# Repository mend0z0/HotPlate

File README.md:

## Latest update

``
Mainly working on Firmware, but modifying file structures and updating readme files are also on-going...
``

# HotPlate

Hot plate project's purpose is to control the temperature of a hot plate that is used for reflow soldering of PCBs in small numbers. The application
will support a camera for more analysis and study of the process of soldering. The application accepts Gerber, Pick&Place, and BOM, so then the 
user will have a full assembly guideline and also with the connected camera it's possible to confirm the quality and validity of placement and assembly.

## Category

__Assembly Automation__

## Features

- Image processing
- Manual assembly guide
- Controlling over any kind of heaters

## Tech Stack

### Hardware

- **MCU:** PIC18F24J50
- **Connection:** USB, SPI
- **PCB Layers:** 4Layer/s (None-controlled Impedance)
- **CAD:** KiCAD

### Firmware

- **OS:** Super loop
- **Programming Language:** C Language
- **IDE:** MPLABX

### Application

- **IDE:** Qt6
- **Operating System:** Linux/Windows
- **Device:** PC/Laptop

### Mechanical

- **CAD:** Solid Edge
- **Manufacturing Method:** 3D Printing

## Block Diagrams

## Screenshots

### Hardware

#### Hardware CAD View

#### 3D_View

#### Assembled Hardware

### Mechanical CAD View

### Final Device

### Application

## Demo

## LOGO

## Author

- [@Siavash Taher Parvar](https://www.linkedin.com/in/mend0z0)

## Support

[Support Link](https://github.com/sponsors/mend0z0)

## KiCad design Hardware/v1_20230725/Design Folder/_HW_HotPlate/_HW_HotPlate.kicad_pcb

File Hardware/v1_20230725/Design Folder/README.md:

# TODO list

HotPlate hardware project todo list.

## Tasks

- #### MUST DO (List the works that proper working of project depends on these tasks):
    - Removing the Header 4x2 from Mechanical parts, and replacing with only 1 recept 1x8.
    - Adding all the mechanical components to the library and schematic.
    - Exporting all the required outputs and finalizing the hardware project.
    - Designing the enclosure in Solidedge.
    - Correcting the stencil outputs. (Next revision)
    - 
- #### Important (List the works that efficient and optimized functionality of project depends on these tasks):
    - Adding 1 more RED LED for +5v power to be placed on the enclosure. (Mechanical parts) (Next revision)
    - Adding 1 more header (2x1, P1.27mm), for +5v output in schematic. (Next revision)
    - Adding Test points for each output power. (Next revision)
    - Correcting the prog pin order according to the output of the programmer. (Next revision)
    - Sizing up the components to 0603 package. (Next revision)
    - Changing the LDO to some bigger package, maybe TL... (Next revision)
    - Modifying the component placement for sure :) (Next revision)
    - Changing the big cap (10uF_400V) to THD. (Next revision)
    - 
- #### General (List tasks that are good to be done but the functionality of project doesn't depend on these):
    - 
    -
    -

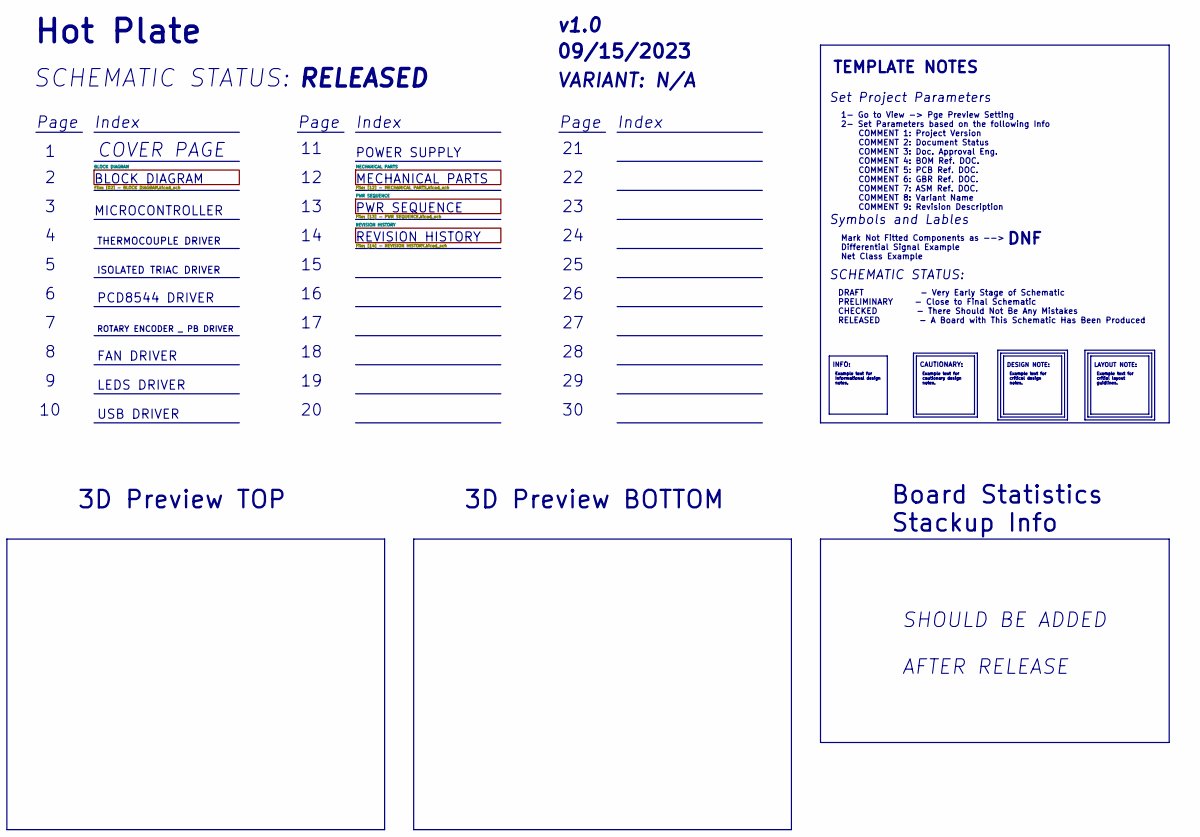
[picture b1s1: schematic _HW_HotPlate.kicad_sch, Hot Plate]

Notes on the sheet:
USB DRIVER
SHOULD BE ADDED AFTER RELEASE
Set Project Parameters
PCD8544 DRIVER
PWR SEQUENCE
VARIANT: ${COMMENT8}
${REVISION}
Index
Example text for critial layout guidlines.
${TITLE}
DESIGN NOTE:
Page
Board Statistics Stackup Info
REVISION HISTORY
${COMMENT2}
COVER PAGE
SCHEMATIC STATUS:
ISOLATED TRIAC DRIVER
MICROCONTROLLER
LEDS DRIVER
Symbols and Lables
TEMPLATE NOTES
THERMOCOUPLE DRIVER
Mark Not Fitted Components as --> Differential Signal Example Net Class Example
${ISSUE_DATE}
Example text for critical design notes.
Example text for Informational design notes.
Example text for cautionary design notes.
INFO:
SCHEMATIC STATUS:
BLOCK DIAGRAM
FAN DRIVER
3D Preview BOTTOM
1- Go to View -> Pge Preview Setting 2- Set Parameters based on the following Info COMMENT 1: Project Version COMMENT 2: Document Status COMMENT 3: Doc. Approval Eng. COMMENT 4: BOM Ref. DOC. COMMENT 5: PCB Ref. DOC. COMMENT 6: GBR Ref. DOC. COMMENT 7: ASM Ref. DOC. COMMENT 8: Variant Name COMMENT 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
LAYOUT NOTE:
CAUTIONARY:
POWER SUPPLY
DRAFT - Very Early Stage of Schematic PRELIMINARY - Close to Final Schematic CHECKED - There Should Not Be Any Mistakes RELEASED - A Board with This Schematic Has Been Produced
MECHANICAL PARTS
DNF

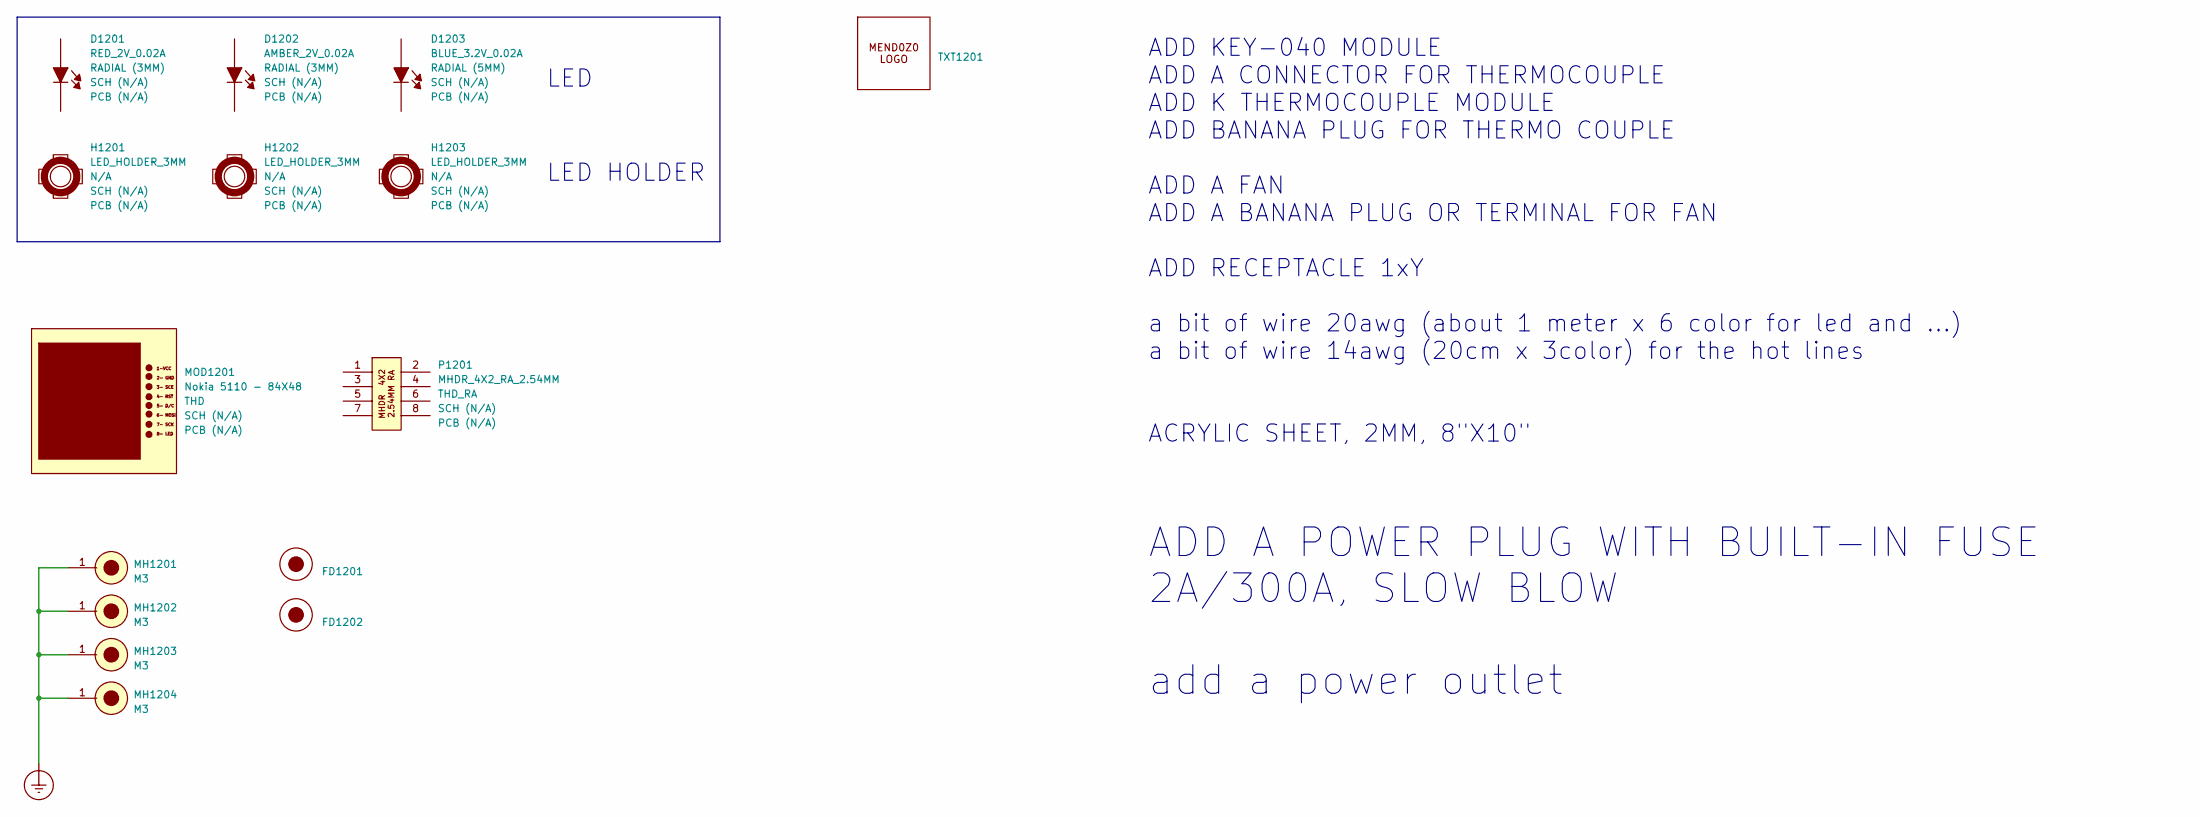
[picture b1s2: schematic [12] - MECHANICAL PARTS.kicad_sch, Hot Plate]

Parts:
D1201: RED_2V_0.02A; LED_D3.0mm; Part Number (Manufactur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 WP7113ID
D1202: AMBER_2V_0.02A; LED_D3.0mm; Part Number (Manufactur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 BL-BJC1V4V-AT
D1203: BLUE_3.2V_0.02A; LED_D5.0mm; Part Number (Manufactur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 151051BS04000
FD1201, FD1202: Fiducial_0.5mm_Mask1mm
H1201, H1202, H1203: LED_HOLDER_3MM; Part Number (Manufactur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 SSH-LX3050
MH1201, MH1202, MH1203, MH1204: M3; MountingHole_3.2mm_M3_DIN965_Pad_TopBottom
MOD1201: Nokia 5110 - 84X48; Part Number Graphic LCD 84x48 - Nokia 5110
P1201: MHDR_4X2_RA_2.54MM; PinHeader_2x04_P2.54mm_Horizontal; Part Number (Manufactur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 PHED-RS008G1ABOGA-C006
TXT1201: Mend0z0_Logo

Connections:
Earth_Protective: MH1201.1, MH1202.1, MH1203.1, MH1204.1; also elsewhere on the board

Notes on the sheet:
LED
ADD KEY-040 MODULE ADD A CONNECTOR FOR THERMOCOUPLE ADD K THERMOCOUPLE MODULE ADD BANANA PLUG FOR THERMO COUPLE ADD A FAN ADD A BANANA PLUG OR TERMINAL FOR FAN ADD RECEPTACLE 1xY a bit of wire 20awg (about 1 meter x 6 color for led and ...) a bit of wire 14awg (20cm x 3color) for the hot lines ACRY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
LED HOLDER
ADD A POWER PLUG WITH BUILT-IN FUSE 2A/300A, SLOW BLOW add a power outlet

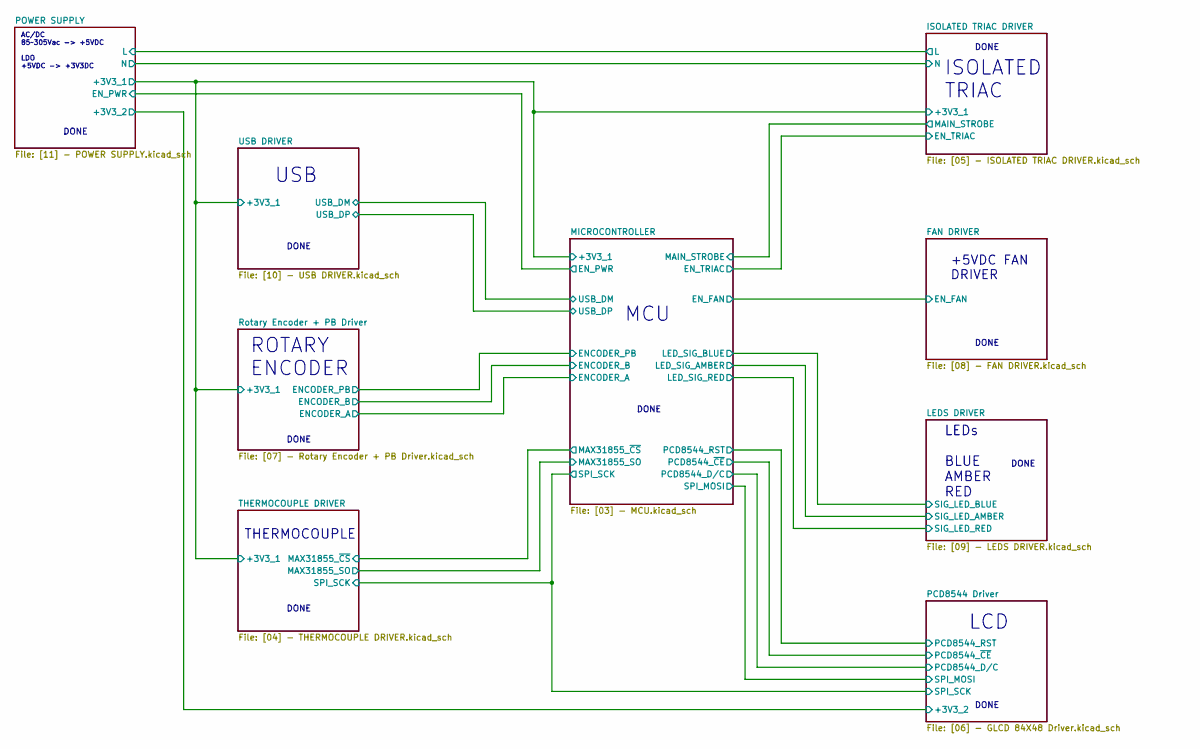
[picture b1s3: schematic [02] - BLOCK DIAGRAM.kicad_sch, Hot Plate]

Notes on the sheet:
DONE
MCU
THERMOCOUPLE
AC/DC 85~305Vac -> +5VDC LDO +5VDC -> +3V3DC
USB
LCD
ROTARY ENCODER
ISOLATED TRIAC
LEDs BLUE AMBER RED
+5VDC FAN DRIVER

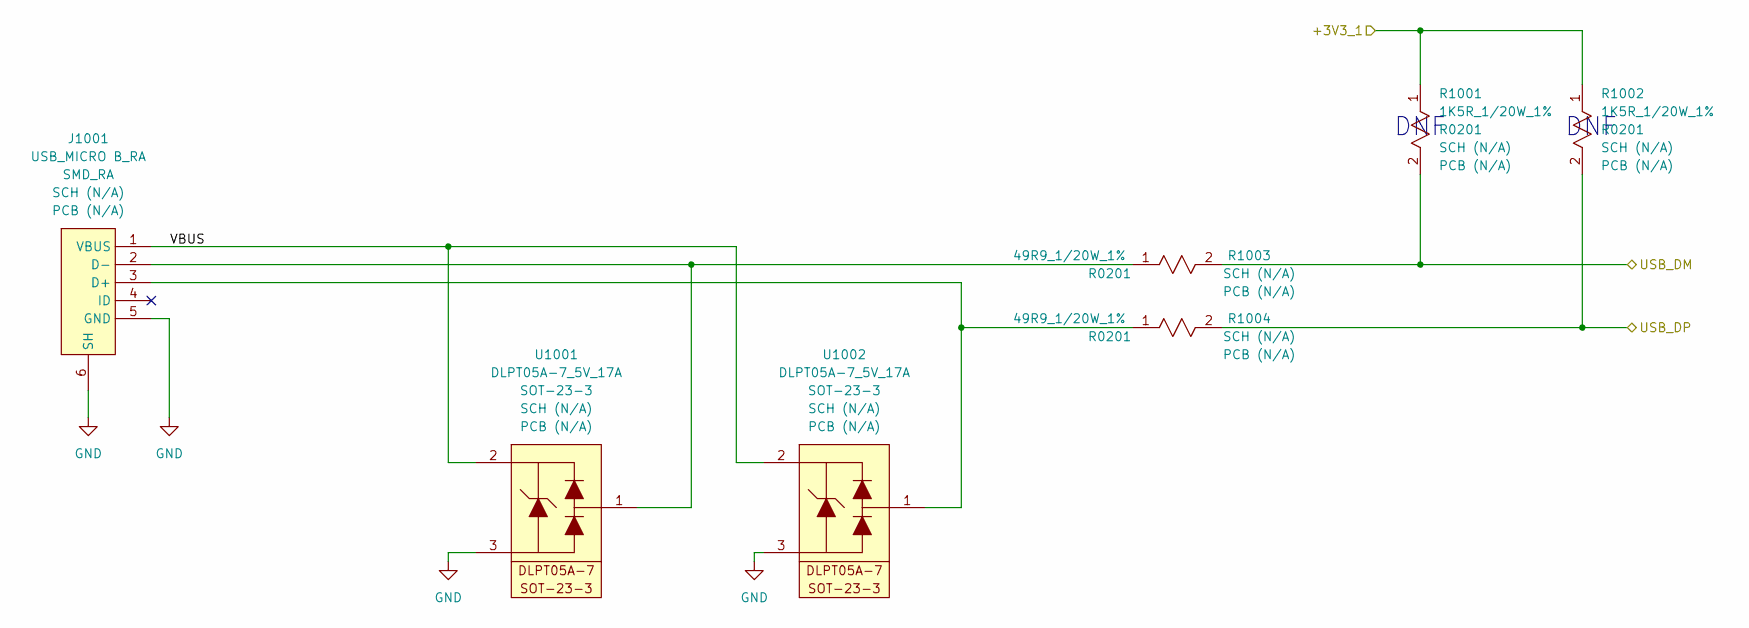
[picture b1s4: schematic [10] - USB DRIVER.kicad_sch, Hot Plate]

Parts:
J1001: USB_MICRO B_RA; USB_Micro-B_Amphenol_10118194_Horizontal; Part Number (Manufactur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 10118194-0001LF
R1001, R1002: 1K5R_1/20W_1%; R_0201_0603Metric; Part Number (Manufactur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 RC0201FR-071K4L
R1003, R1004: 49R9_1/20W_1%; R_0201_0603Metric; Part Number (Manufactur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 RMCF0201FT49R9
U1001, U1002: DLPT05A-7_5V_17A; SOT-23; Part Number (Manufactur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 DLPT05A-7

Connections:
/BLOCK DIAGRAM/ISOLATED TRIAC DRIVER/+3V3_1: R1001.1, R1002.1; also elsewhere on the board
/BLOCK DIAGRAM/MICROCONTROLLER/USB_DM: R1001.2, R1003.2; also elsewhere on the board
/BLOCK DIAGRAM/MICROCONTROLLER/USB_DP: R1002.2, R1004.2; also elsewhere on the board
/BLOCK DIAGRAM/USB DRIVER/VBUS: J1001.1 (VBUS), U1001.2, U1002.2
unnamed: J1001.3 (D+), R1004.1, U1002.1
unnamed: J1001.2 (D-), R1003.1, U1001.1

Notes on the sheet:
DNF

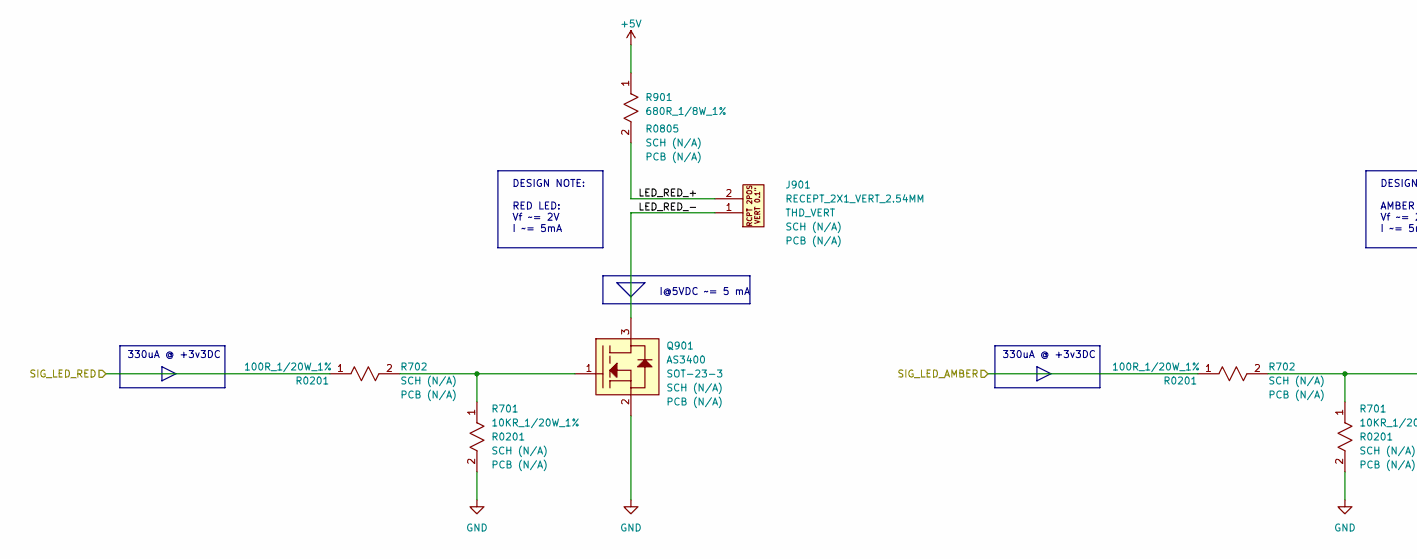
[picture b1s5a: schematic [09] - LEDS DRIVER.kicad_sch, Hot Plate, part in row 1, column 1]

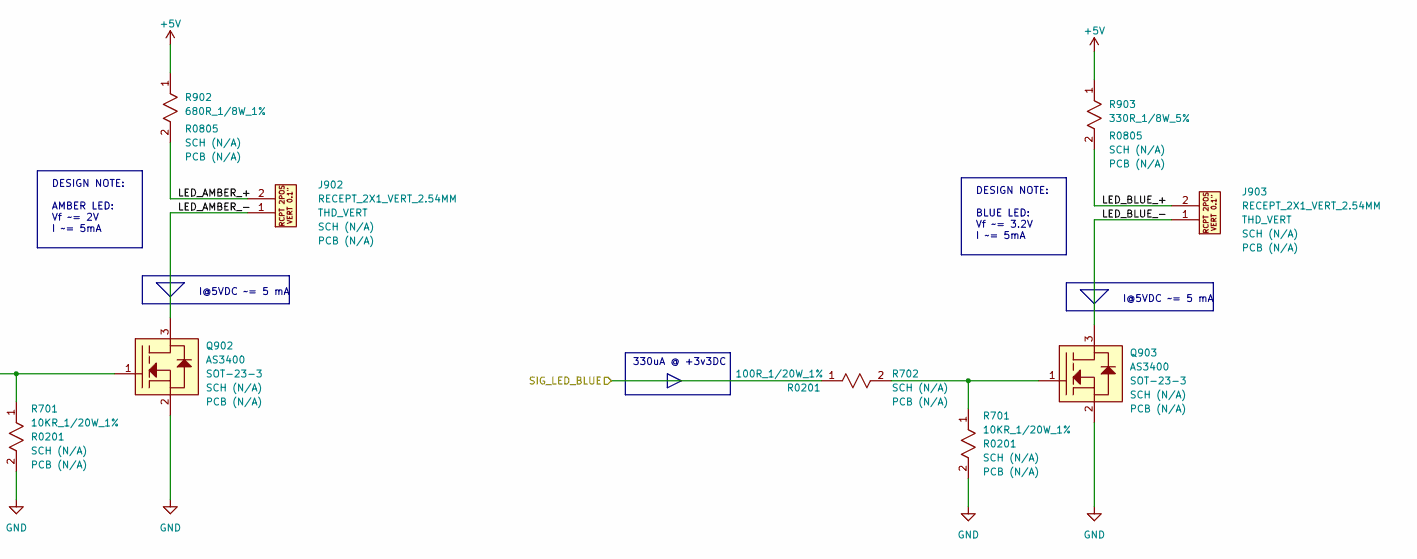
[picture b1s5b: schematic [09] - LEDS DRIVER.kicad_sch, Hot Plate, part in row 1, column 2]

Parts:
J901, J902, J903: RECEPT_2X1_VERT_2.54MM; PinSocket_1x02_P2.54mm_Vertical; Part Number (Manufactur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 RS1-02-G
Q901, Q902, Q903: AS3400; SOT-23; Part Number (Manufactur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 AS3400
R701: 10KR_1/20W_1%; R_0201_0603Metric; Part Number (Manufactur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 RMCF0201FT10K0
R702: 100R_1/20W_1%; R_0201_0603Metric; Part Number (Manufactur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 RMCF0201FT100R
R901, R902: 680R_1/8W_1%; R_0805_2012Metric; Part Number (Manufactur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 AC0805FR-07680RL
R903: 330R_1/8W_5%; R_0805_2012Metric; Part Number (Manufactur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 CRGCQ0805J330R

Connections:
/BLOCK DIAGRAM/LEDS DRIVER/LED_AMBER_+: J902.2, R902.2
/BLOCK DIAGRAM/LEDS DRIVER/LED_AMBER_-: J902.1, Q902.3
/BLOCK DIAGRAM/LEDS DRIVER/LED_RED_+: J901.2, R901.2
/BLOCK DIAGRAM/LEDS DRIVER/LED_RED_-: J901.1, Q901.3
unnamed 68: R702.1; also elsewhere on the board

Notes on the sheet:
DESIGN NOTE: AMBER LED: Vf ~= 2V I ~= 5mA
I@5VDC ~= 5 mA
DESIGN NOTE: BLUE LED: Vf ~= 3.2V I ~= 5mA
330uA @ +3v3DC
DESIGN NOTE: RED LED: Vf ~= 2V I ~= 5mA

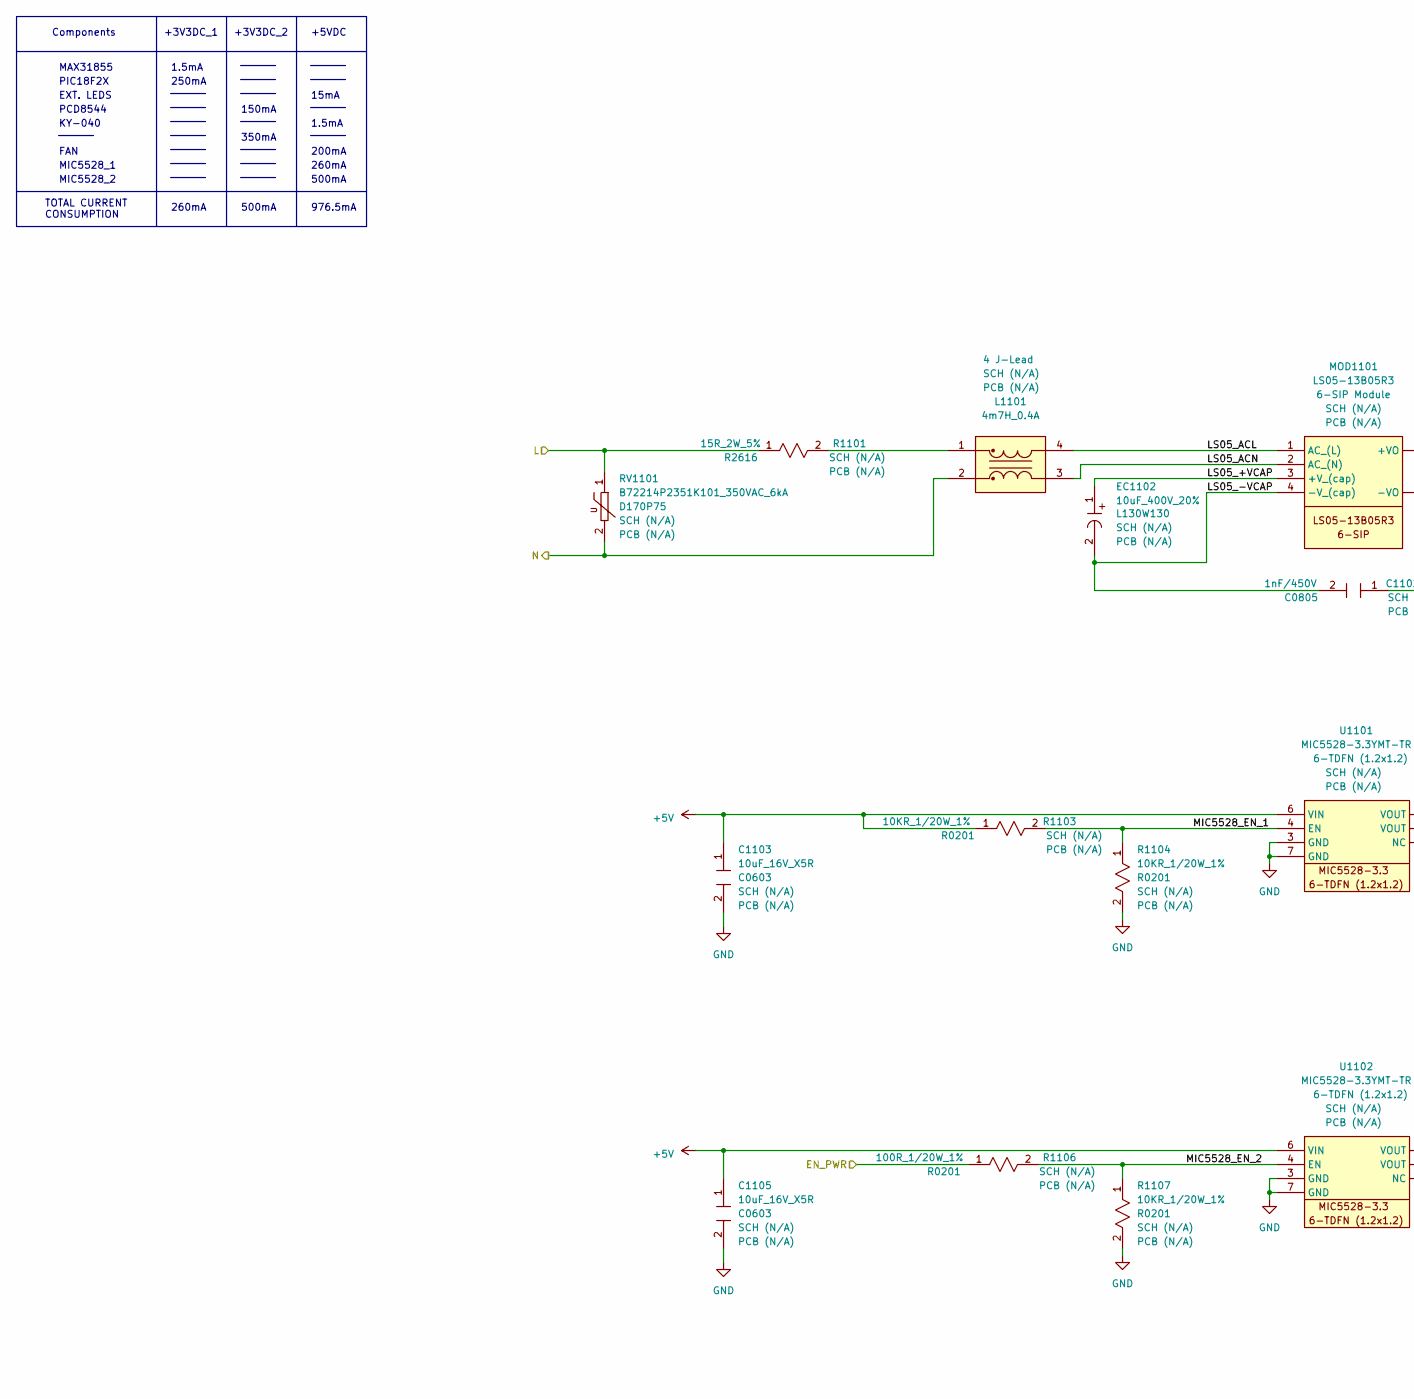
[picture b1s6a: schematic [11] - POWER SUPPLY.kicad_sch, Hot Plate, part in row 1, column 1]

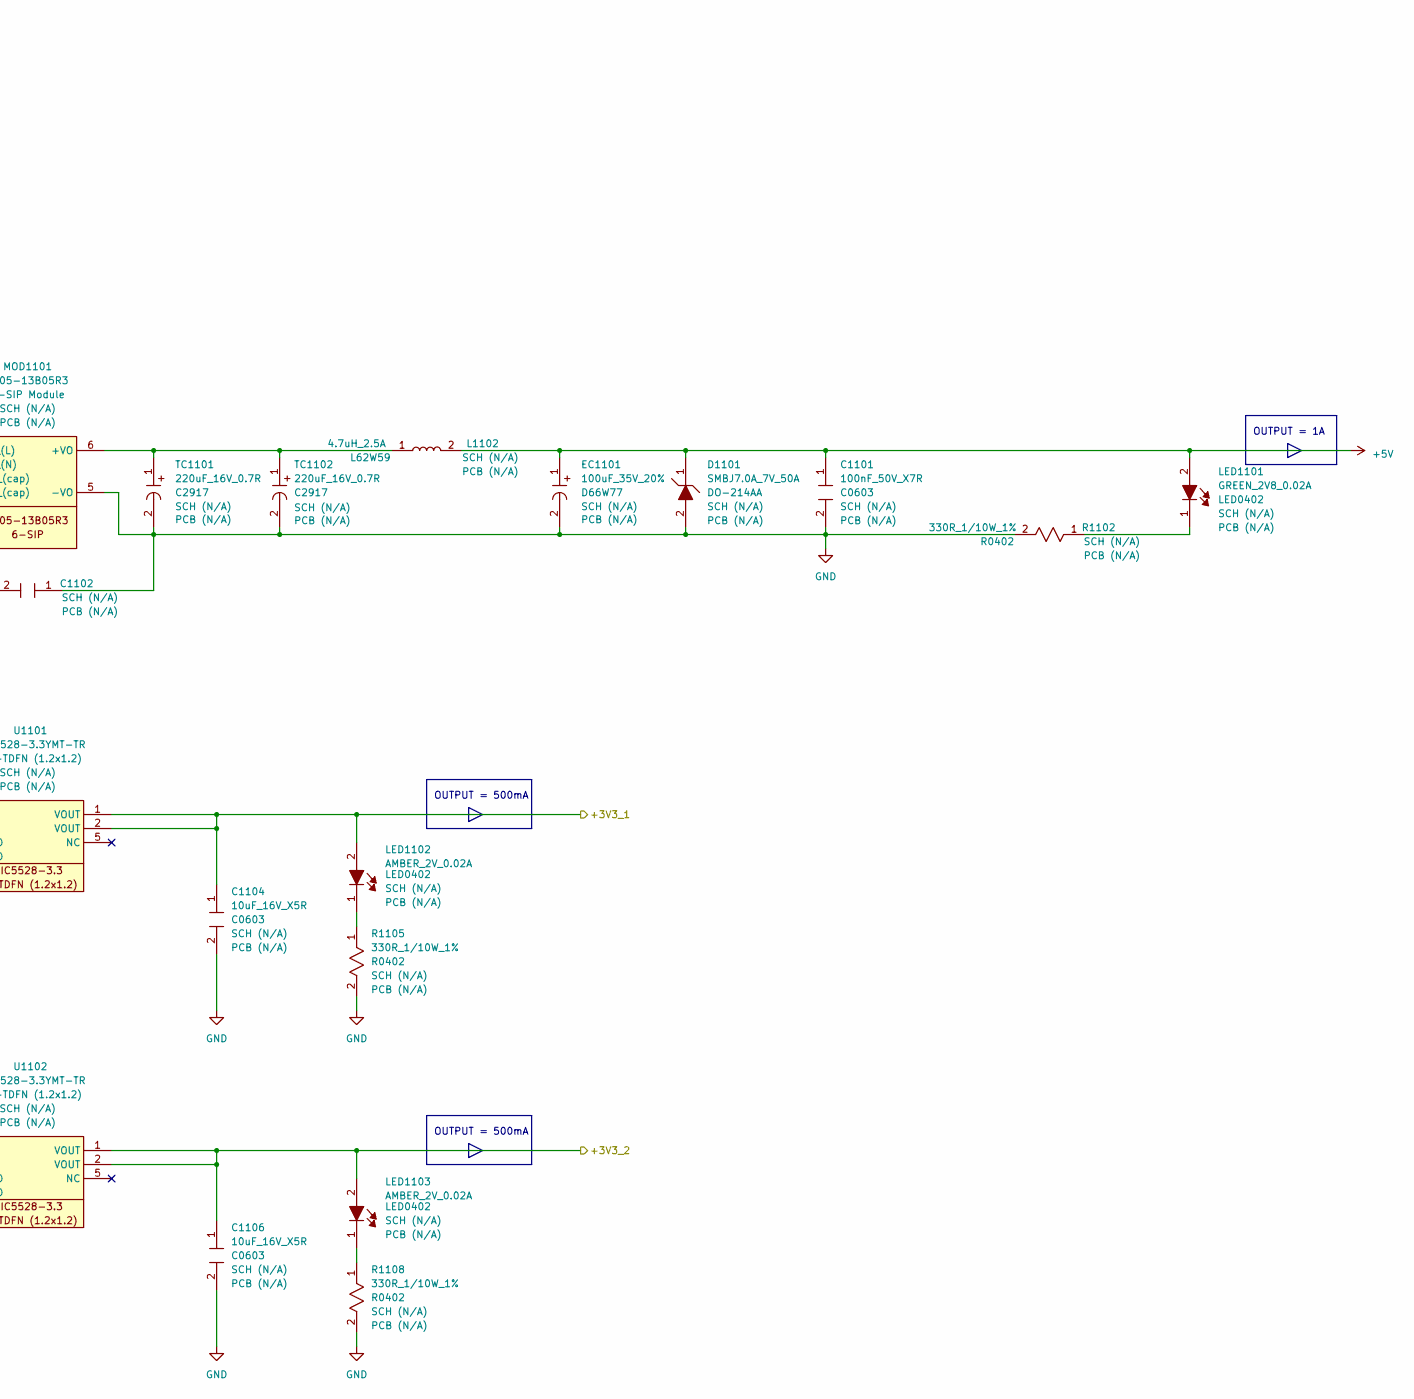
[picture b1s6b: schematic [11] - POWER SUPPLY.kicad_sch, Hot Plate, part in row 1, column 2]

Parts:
C1101: 100nF_50V_X7R; C_0603_1608Metric; Part Number (Manufactur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 CL10B104KB8NNNC
C1102: 1nF/450V; C_0805_2012Metric; Part Number CGA4C4C0G2W102J060AE
C1103, C1104, C1105, C1106: 10uF_16V_X5R; C_0603_1608Metric; Part Number (Manufactur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 GRT188R61C106KE13J
D1101: SMBJ7.0A_7V_50A; D_SMB; Part Number (Manufactur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 SMBJ7.0A
EC1101: 100uF_35V_20%; CP_Elec_6.3x7.7; Part Number (Manufactur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 AFK107M35X16T-F
EC1102: 10uF_400V_20%; CAP_S-V_12P5X13P5_RUB; Part Number (Manufactur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 400SGV10M12.5X13.5
L1101: 4m7H_0.4A; IND_50XXXC_MUR; Part Number (Manufactur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 50475C
L1102: 4.7uH_2.5A; IND_6045_TDK; Part Number (Manufactur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 CLF6045T-4R7N-H
LED1101: GREEN_2V8_0.02A; LED_0402_1005Metric; Part Number (Manufactur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 B2841NG--05D000514U1930
LED1102, LED1103: AMBER_2V_0.02A; LED_0402_1005Metric; Part Number (Manufactur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 B2841UY--20D000414U1930
MOD1101: LS05-13B05R3; CONV_LS05-13B05R3; Part Number (Manufactur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 LS05-13B05R3
R1101: 15R_2W_5%; RES_SMF2_TYCO_TYC; Part Number (Manufactur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 SMW215RJT
R1102, R1105, R1108: 330R_1/10W_1%; R_0402_1005Metric; Part Number (Manufactur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 ERJ-2RKF3300X
R1103, R1104, R1107: 10KR_1/20W_1%; R_0201_0603Metric; Part Number (Manufactur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 RMCF0201FT10K0
R1106: 100R_1/20W_1%; R_0201_0603Metric; Part Number (Manufactur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 RMCF0201FT100R
RV1101: B72214P2351K101_350VAC_6kA; RV_Disc_D16.5mm_W6.7mm_P7.5mm; Part Number (Manufactur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 B72214P2351K101
TC1101, TC1102: 220uF_16V_0.7R; CP_EIA-7343-30_AVX-N; Part Number (Manufactur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 F931C227MNC
U1101, U1102: MIC5528-3.3YMT-TR; DFN-6-1EP_1.2x1.2mm_P0.4mm_EP0.3x0.94mm_PullBack; Part Number (Manufactur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 MIC5528-3.3YMT-TR

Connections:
/BLOCK DIAGRAM/ISOLATED TRIAC DRIVER/+3V3_1: C1104.1, LED1102.2, U1101.1 (VOUT), U1101.2 (VOUT); also elsewhere on the board
/BLOCK DIAGRAM/ISOLATED TRIAC DRIVER/L_IN: R1101.1, RV1101.1; also elsewhere on the board
/BLOCK DIAGRAM/ISOLATED TRIAC DRIVER/N: L1101.2, RV1101.2; also elsewhere on the board
/BLOCK DIAGRAM/MICROCONTROLLER/EN_PWR: R1106.1; also elsewhere on the board
/BLOCK DIAGRAM/PCD8544 Driver/+3V3_2: C1106.1, LED1103.2, U1102.1 (VOUT), U1102.2 (VOUT); also elsewhere on the board
/BLOCK DIAGRAM/POWER SUPPLY/LS05_+VCAP: EC1102.1, MOD1101.3 (+V_(cap))
/BLOCK DIAGRAM/POWER SUPPLY/LS05_-VCAP: C1102.2, EC1102.2, MOD1101.4 (-V_(cap))
/BLOCK DIAGRAM/POWER SUPPLY/LS05_ACL: L1101.4, MOD1101.1 (AC_(L))
/BLOCK DIAGRAM/POWER SUPPLY/LS05_ACN: L1101.3, MOD1101.2 (AC_(N))
/BLOCK DIAGRAM/POWER SUPPLY/MIC5528_EN_1: R1103.2, R1104.1, U1101.4 (EN)
/BLOCK DIAGRAM/POWER SUPPLY/MIC5528_EN_2: R1106.2, R1107.1, U1102.4 (EN)
unnamed: L1101.1, R1101.2
unnamed: LED1101.1, R1102.1
unnamed: LED1102.1, R1105.1
unnamed: LED1103.1, R1108.1
unnamed: L1102.1, MOD1101.6 (+VO), TC1101.1, TC1102.1

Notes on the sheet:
+5VDC
500mA
260mA
350mA
1.5mA
PIC18F2X
TOTAL CURRENT CONSUMPTION
EXT. LEDS
150mA
Components
200mA
+3V3DC_1
FAN
15mA
OUTPUT = 500mA
976.5mA
+3V3DC_2
MIC5528_1
PCD8544
250mA
OUTPUT = 1A
MAX31855
MIC5528_2
KY-040

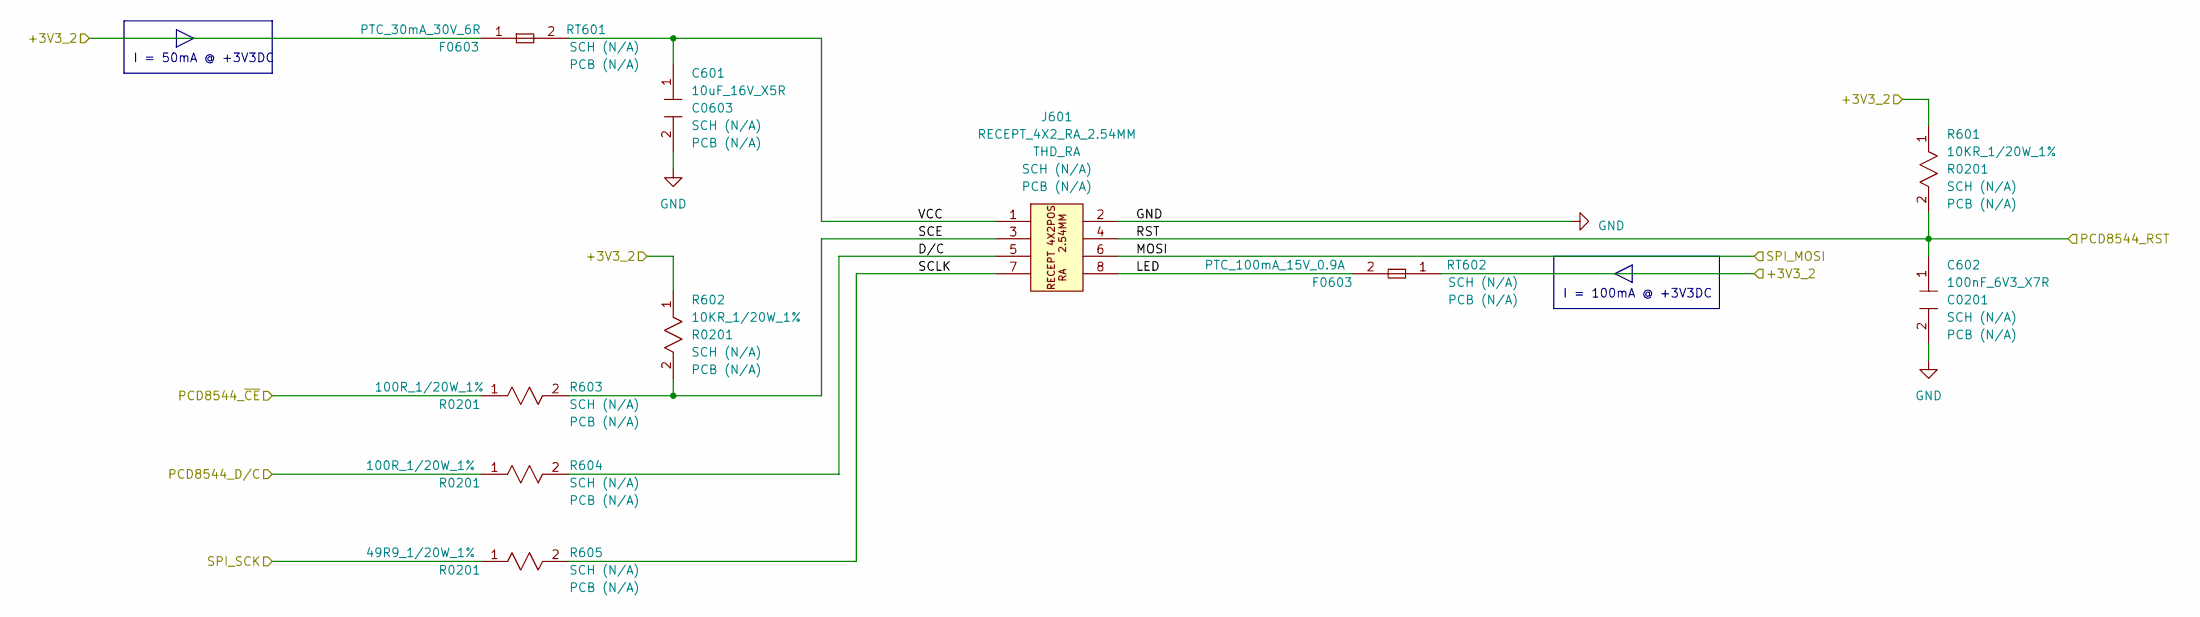
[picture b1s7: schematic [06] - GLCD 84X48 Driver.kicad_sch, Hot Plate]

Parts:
C601: 10uF_16V_X5R; C_0603_1608Metric; Part Number (Manufactur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 GRT188R61C106KE13J
C602: 100nF_6V3_X7R; C_0201_0603Metric; Part Number (Manufactur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 CC0201KRX7R5BB104
J601: RECEPT_4X2_RA_2.54MM; PinSocket_2x04_P2.54mm_Horizontal; Part Number (Manufactur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 PPTC042LJBN-RC
R601, R602: 10KR_1/20W_1%; R_0201_0603Metric; Part Number (Manufactur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 RMCF0201FT10K0
R603, R604: 100R_1/20W_1%; R_0201_0603Metric; Part Number (Manufactur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 RMCF0201FT100R
R605: 49R9_1/20W_1%; R_0201_0603Metric; Part Number (Manufactur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 RMCF0201FT49R9
RT601: PTC_30mA_30V_6R; Fuse_0603_1608Metric; Part Number (Manufactur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 0ZCM0003FF2G
RT602: PTC_100mA_15V_0.9A; Fuse_0603_1608Metric; Part Number (Manufactur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 0ZCM0010FF2G

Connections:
/BLOCK DIAGRAM/MICROCONTROLLER/PCD8544_D/C: R604.1; also elsewhere on the board
/BLOCK DIAGRAM/MICROCONTROLLER/PCD8544_~CE: R603.1; also elsewhere on the board
/BLOCK DIAGRAM/MICROCONTROLLER/SPI_SCK: R605.1; also elsewhere on the board
/BLOCK DIAGRAM/PCD8544 Driver/+3V3_2: R601.1, R602.1, RT601.1, RT602.1; also elsewhere on the board
/BLOCK DIAGRAM/PCD8544 Driver/D/C: J601.5, R604.2
/BLOCK DIAGRAM/PCD8544 Driver/LED: J601.8, RT602.2
/BLOCK DIAGRAM/PCD8544 Driver/MOSI: J601.6; also elsewhere on the board
/BLOCK DIAGRAM/PCD8544 Driver/RST: C602.1, J601.4, R601.2; also elsewhere on the board
/BLOCK DIAGRAM/PCD8544 Driver/SCE: J601.3, R602.2, R603.2
/BLOCK DIAGRAM/PCD8544 Driver/SCLK: J601.7, R605.2
/BLOCK DIAGRAM/PCD8544 Driver/VCC: C601.1, J601.1, RT601.2

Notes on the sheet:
I = 100mA @ +3V3DC
I = 50mA @ +3V3DC

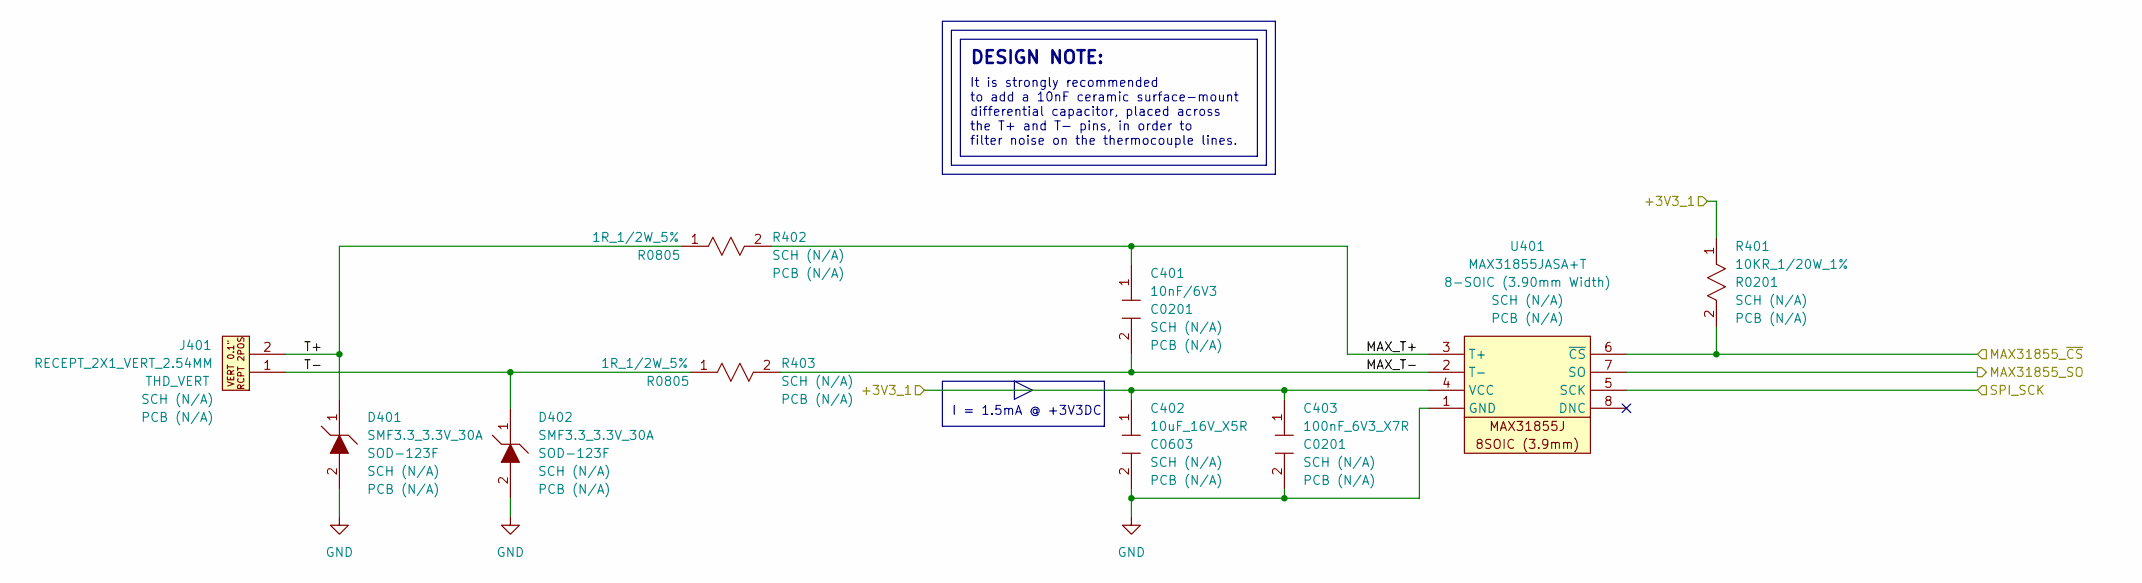
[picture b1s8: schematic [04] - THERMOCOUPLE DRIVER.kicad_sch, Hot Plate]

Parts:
C401: 10nF/6V3; C_0201_0603Metric; Part Number (Manufactur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 0201B103K6R3CT
C402: 10uF_16V_X5R; C_0603_1608Metric; Part Number (Manufactur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 GRT188R61C106KE13J
C403: 100nF_6V3_X7R; C_0201_0603Metric; Part Number (Manufactur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 CC0201KRX7R5BB104
D401, D402: SMF3.3_3.3V_30A; D_SOD-123F; Part Number (Manufactur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 SMF3.3
J401: RECEPT_2X1_VERT_2.54MM; PinSocket_1x02_P2.54mm_Vertical; Part Number (Manufactur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 RS1-02-G
R401: 10KR_1/20W_1%; R_0201_0603Metric; Part Number (Manufactur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 RMCF0201FT10K0
R402, R403: 1R_1/2W_5%; R_0805_2012Metric; Part Number (Manufactur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 SG73P2ATTD1R0J
U401: MAX31855JASA+T; SOIC-8_3.9x4.9mm_P1.27mm; Part Number (Manufactur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 MAX31855JASA+T

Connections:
/BLOCK DIAGRAM/ISOLATED TRIAC DRIVER/+3V3_1: C402.1, C403.1, R401.1, U401.4 (VCC); also elsewhere on the board
/BLOCK DIAGRAM/MICROCONTROLLER/MAX31855_SO: U401.7 (SO); also elsewhere on the board
/BLOCK DIAGRAM/MICROCONTROLLER/MAX31855_~CS: R401.2, U401.6 (~CS); also elsewhere on the board
/BLOCK DIAGRAM/MICROCONTROLLER/SPI_SCK: U401.5 (SCK); also elsewhere on the board
/BLOCK DIAGRAM/THERMOCOUPLE DRIVER/MAX_T+: C401.1, R402.2, U401.3 (T+)
/BLOCK DIAGRAM/THERMOCOUPLE DRIVER/MAX_T-: C401.2, R403.2, U401.2 (T-)
/BLOCK DIAGRAM/THERMOCOUPLE DRIVER/T+: D401.1, J401.2, R402.1
/BLOCK DIAGRAM/THERMOCOUPLE DRIVER/T-: D402.1, J401.1, R403.1

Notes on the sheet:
DESIGN NOTE:
I = 1.5mA @ +3V3DC
It is strongly recommended to add a 10nF ceramic surface-mount differential capacitor, placed across the T+ and T- pins, in order to filter noise on the thermocouple lines.

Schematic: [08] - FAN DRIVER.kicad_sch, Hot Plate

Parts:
D801: BAT60JFILM_10V_3A; D_SOD-323; Part Number (Manufactur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 BAT60JFILM
J903: RECEPT_2X1_VERT_2.54MM; PinSocket_1x02_P2.54mm_Vertical; Part Number (Manufactur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 RS1-02-G
Q801: AS3400; SOT-23; Part Number (Manufactur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 AS3400
R801: 100R_1/20W_1%; R_0201_0603Metric; Part Number (Manufactur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 RMCF0201FT100R
R802: 10KR_1/20W_1%; R_0201_0603Metric; Part Number (Manufactur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 RMCF0201FT10K0
RT801: PTC_100mA_15V_0.9A; Fuse_0603_1608Metric; Part Number (Manufactur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 0ZCM0010FF2G

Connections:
/BLOCK DIAGRAM/FAN DRIVER/EN_FAN: R801.1; also elsewhere on the board
unnamed: Q801.1, R801.2, R802.1

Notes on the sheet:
330uA @ +3v3DC
0.1A @ 4.5VDC

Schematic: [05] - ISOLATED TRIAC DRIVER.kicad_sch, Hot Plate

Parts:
D501: S1J_600V_1A; D_SMA; Part Number (Manufactur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 S1J
J501, J502: TERM_3POS_SIDE_5.08MM; TerminalBlock_Phoenix_MKDS-1,5-3-5.08_1x03_P5.08mm_Horizont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; Part Number (Manufactur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 EB147A-03-D
Q501: T2050H-6G-TR_600V_20A; TO-263-2; Part Number (Manufactur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 T2050H-6G-TR
R501: 10KR_1/20W_1%; R_0201_0603Metric; Part Number (Manufactur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 RMCF0201FT10K0
R502: 100KR_1W_1%; R_MELF_MMB-0207; Part Number (Manufactur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 SMM02070C1003FBP00
R503: 3KR_2W_1%; R_2512_6332Metric; Part Number (Manufactur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 35213K0FT
R504: 330R_1/10W_1%; R_0402_1005Metric; Part Number (Manufactur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 ERJ-2RKF3300X
U501: 140817143400; SMDIP-4_W7.62mm; Part Number (Manufactur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 140817143400
U502: MOC3022S; SMDIP-6_W7.62mm; Part Number (Manufactur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 MOC3022S

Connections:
/BLOCK DIAGRAM/ISOLATED TRIAC DRIVER/+3V3_1: R501.1; also elsewhere on the board
/BLOCK DIAGRAM/ISOLATED TRIAC DRIVER/EN_TRIAC: R504.1; also elsewhere on the board
/BLOCK DIAGRAM/ISOLATED TRIAC DRIVER/L_IN: J502.2, Q501.1, R502.2, R503.1; also elsewhere on the board
/BLOCK DIAGRAM/ISOLATED TRIAC DRIVER/L_OUT: J501.2, Q501.2
/BLOCK DIAGRAM/ISOLATED TRIAC DRIVER/MAIN_STROBE: R501.2, U501.4; also elsewhere on the board
/BLOCK DIAGRAM/ISOLATED TRIAC DRIVER/N: D501.1, J501.1, J502.3; also elsewhere on the board
Earth_Protective: J501.3, J502.1; also elsewhere on the board
unnamed: D501.2, U501.2
unnamed: Q501.3, U502.4
unnamed: R502.1, U501.1
unnamed: R503.2, U502.6
unnamed: R504.2, U502.1

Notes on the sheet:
input voltage
I = 6mA @ +3V3DC
+120V / +240V
+3V3DC
I = 1mA @ 110V
+110V
10mA @ 30 Vac 50mA @ 150 Vac 70mA @ 210 Vac (not very compatible with 240 Vac)
CLEAN SIDE
DESIGN NOTE: The Idea for finding the zero-crossing point is by capturing the positive peeks value and then derive the zero point IMPORTANT: Opto Ion = 1mA, Von = 0.9V, V Rectifier diode = 0.7V Von : (0.001A * 100KR) + 0.9 + 0.7 ~= +110V It's possible to figure out the frequency and working voltage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
-120V / -240V
MCU pin

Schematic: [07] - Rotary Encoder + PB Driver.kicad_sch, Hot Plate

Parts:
C701, C702, C704: 10uF_16V_X5R; C_0603_1608Metric; Part Number (Manufactur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 GRT188R61C106KE13J
C703: 100nF_6V3_X7R; C_0201_0603Metric; Part Number (Manufactur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 CC0201KRX7R5BB104
J701: RECEPT_5X1_RA_2.54MM; PinSocket_1x05_P2.54mm_Horizontal; Part Number (Manufactur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 PPTC051LGBN-RC
R701, R703, R705: 10KR_1/20W_1%; R_0201_0603Metric; Part Number (Manufactur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 RMCF0201FT10K0
R702, R704, R706: 100R_1/20W_1%; R_0201_0603Metric; Part Number (Manufactur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 RMCF0201FT100R
U701, U702, U704: SN74LVC1G17DBVR; SOT-23-5; Part Number (Manufactur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 SN74LVC1G17DBVR
U703: DLPT05A-7_5V_17A; SOT-23; Part Number (Manufactur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 DLPT05A-7

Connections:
/BLOCK DIAGRAM/ISOLATED TRIAC DRIVER/+3V3_1: C701.1, C702.1, C704.1, U701.5 (VCC), U702.5 (VCC), U704.5 (VCC); also elsewhere on the board
/BLOCK DIAGRAM/MICROCONTROLLER/ENCODER_PB: R706.2; also elsewhere on the board
/BLOCK DIAGRAM/MICROCONTROLLER/PIC18_ICSPPGC: R704.2; also elsewhere on the board
/BLOCK DIAGRAM/Rotary Encoder + PB Driver/KEY-040_B: J701.2, R703.2, U702.2 (A)
/BLOCK DIAGRAM/Rotary Encoder + PB Driver/KEY-040_SW: C703.1, J701.3, R705.2, U703.1, U704.2 (A)
unnamed: R702.1, U701.4 (Y)
unnamed: R704.1, U702.4 (Y)
unnamed: R706.1, U704.4 (Y)

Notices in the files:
Hardware/v1_20230725/Design Folder/_HW_HotPlate/_HW_HotPlate.kicad_pcb:
(c) Siavash Taher Parvar All Rights Reserved
